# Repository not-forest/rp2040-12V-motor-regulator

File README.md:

# RP2040-Zero Powered 12V Motor Controller

RP2040 microcontroller handles status LEDs, an H-Bridge driver, and a rotary encoder input. RP2040's **PIO** is used to read encoder signals as a state machine, completely restraining bouncing errors from the input lines. This allows to use cheap encoders and have an amazing precision.

---

---

### PCB
- Designed in **KiCad**.
- Screw terminals 12V power input and motor output.
- Two versions include buck converter and linear regulator.

---

## Software
1. **Rotary Encoder**:
   - PIO reads encoder signals and adjusts speed.
2. **Rotary Encoder's Switch**:
   - Changes motor direction via the H-Bridge.
3. **PWM**:
   - Controls motor speed by adjusting duty cycles.
4. **Status LEDs**:
   - Show real-time speed and direction updates.

---

### Requirements
- **Rust Toolchain**: For building firmware.
- **elf2uf2-rs**: To flash the RP2040 (`cargo run` automatically searches for connected rp2040 and flashes thefirmware).
- **KiCad**: adjust PCB design.

---

Provides a reference for PIO-based rotary encoder handling in Rust.

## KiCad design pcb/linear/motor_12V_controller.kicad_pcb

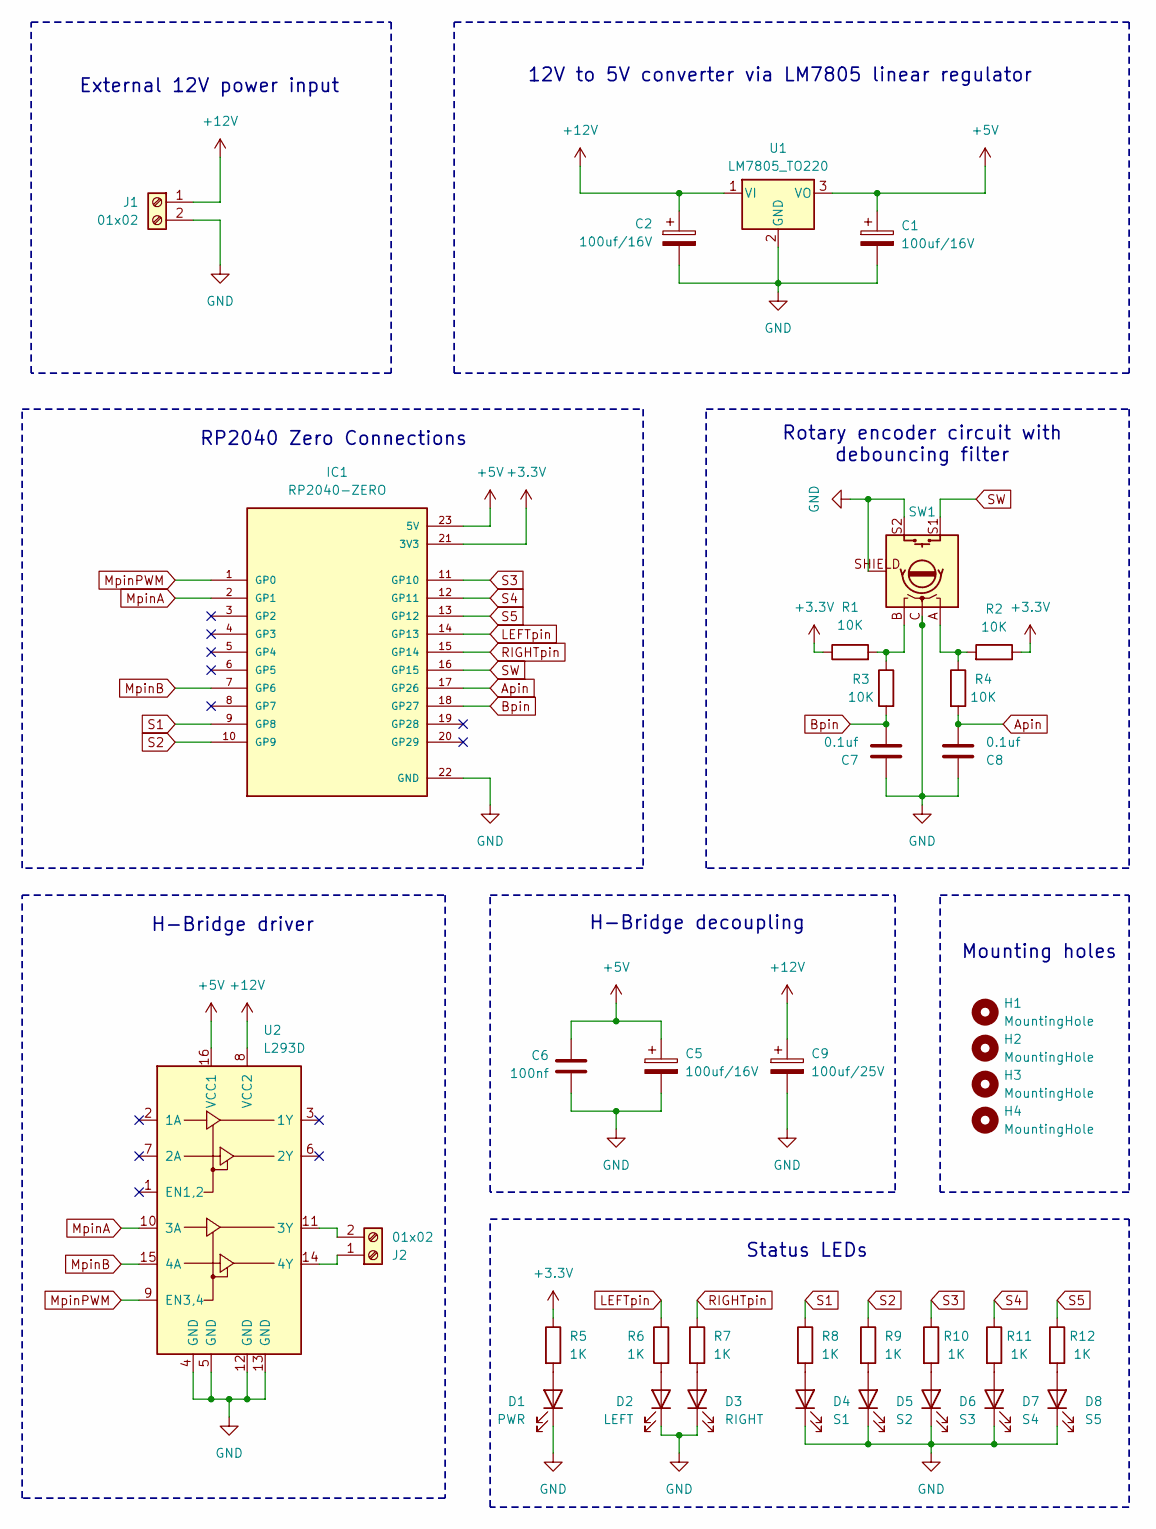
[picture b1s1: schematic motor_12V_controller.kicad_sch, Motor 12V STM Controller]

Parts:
C1, C2: 100uf/16V; C_Disc_D3.0mm_W1.6mm_P2.50mm
C5: 100uf/16V; C_Disc_D3.0mm_W2.0mm_P2.50mm
C6: 100nf; CP_Radial_D4.0mm_P1.50mm
C7, C8: 0.1uf; CP_Radial_D4.0mm_P1.50mm
C9: 100uf/25V; C_Disc_D3.0mm_W2.0mm_P2.50mm
D1: PWR; LED_Rectangular_W5.0mm_H2.0mm
D2: LEFT; LED_Rectangular_W5.0mm_H2.0mm
D3: RIGHT; LED_Rectangular_W5.0mm_H2.0mm
D4: S1; LED_Rectangular_W5.0mm_H2.0mm
D5: S2; LED_Rectangular_W5.0mm_H2.0mm
D6: S3; LED_Rectangular_W5.0mm_H2.0mm
D7: S4; LED_Rectangular_W5.0mm_H2.0mm
D8: S5; LED_Rectangular_W5.0mm_H2.0mm
H1, H2, H3, H4: MountingHole; MountingHole_2.2mm_M2
IC1: RP2040-ZERO; MODULE_RP2040-ZERO; PARTREV NA
J1, J2: 01x02; TerminalBlock_Xinya_XY308-2.54-2P_1x02_P2.54mm_Horizontal
R1, R2, R3, R4: 10K; R_Axial_DIN0204_L3.6mm_D1.6mm_P2.54mm_Vertical
R5, R6, R7, R8, R9, R10, R11, R12: 1K; R_Axial_DIN0204_L3.6mm_D1.6mm_P2.54mm_Vertical
SW1: XDCR_PEC11R-4215F-S0024
U1: LM7805_TO220; TO-220-3_Vertical
U2: L293D; DIP-16_W7.62mm_LongPads

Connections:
+3.3V: IC1.21 (3V3), R1.1, R2.1, R5.1
+5V: C1.1, C5.1, C6.1, IC1.23 (5V), U1.3 (VO), U2.16 (VCC1)
+12V: C2.1, C9.1, J1.1, U1.1 (VI), U2.8 (VCC2)
Apin: C8.2, IC1.17 (GP26), R4.2
Bpin: C7.2, IC1.18 (GP27), R3.2
GND: C1.2, C2.2, C5.2, C6.2, C7.1, C8.1, C9.2, D1.1 (K), D2.1 (K), D3.1 (K), D4.1 (K), D5.1 (K), D6.1 (K), D7.1 (K), D8.1 (K), IC1.22 (GND), J1.2, SW1.C, SW1.S2, SW1.SHIELD, U1.2 (GND), U2.4 (GND), U2.5 (GND), U2.12 (GND), U2.13 (GND)
LEFTpin: IC1.14 (GP13), R6.1
MpinA: IC1.2 (GP1), U2.10 (3A)
MpinB: IC1.7 (GP6), U2.15 (4A)
MpinPWM: IC1.1 (GP0), U2.9 (EN3,4)
unnamed: D1.2 (A), R5.2
unnamed: D2.2 (A), R6.2
unnamed: D3.2 (A), R7.2
unnamed: D4.2 (A), R8.2
unnamed: D5.2 (A), R9.2
unnamed: D6.2 (A), R10.2
unnamed: D7.2 (A), R11.2
unnamed: D8.2 (A), R12.2
unnamed: J2.1, U2.14 (4Y)
unnamed: J2.2, U2.11 (3Y)
unnamed: R1.2, R3.1, SW1.B
unnamed: R2.2, R4.1, SW1.A
RIGHTpin: IC1.15 (GP14), R7.1
S1: IC1.9 (GP8), R8.1
S2: IC1.10 (GP9), R9.1
S3: IC1.11 (GP10), R10.1
S4: IC1.12 (GP11), R11.1
S5: IC1.13 (GP12), R12.1
SW: IC1.16 (GP15), SW1.S1

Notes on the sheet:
Mounting holes
Rotary encoder circuit with debouncing filter
12V to 5V converter via LM7805 linear regulator
External 12V power input
RP2040 Zero Connections
H-Bridge decoupling
H-Bridge driver
Status LEDs

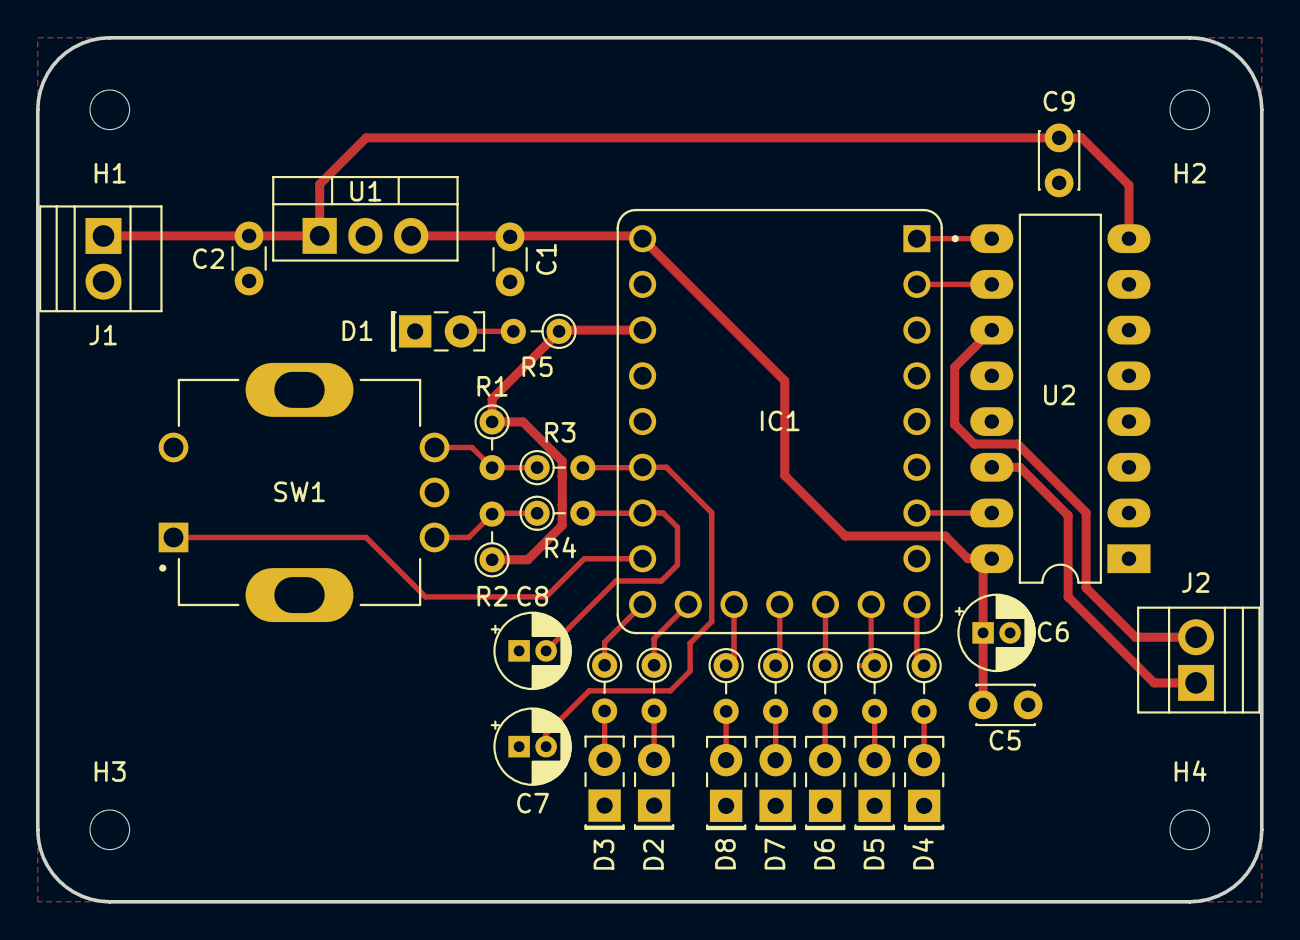
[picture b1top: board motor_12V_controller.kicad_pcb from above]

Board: 2 copper layers, 68.0 x 48.0 mm, 37 parts (0 on the bottom side), 29 nets.

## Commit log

2024-10-31 Added the first schematic layout and RP2040 Zero symbol file.
2024-10-31 Swapped the connections to to create more compact PCB design.
2024-10-31 Added more symbols and 3d models for PCB design.
2024-10-31 Added the first PCB design layout for a single layered, SMD, ground plane solution. Some changes might appear when implementing the source code or searching for components.
2024-10-31 Added the minimal rp2040 firmware code.
2024-10-31 Added the memory layout linker script stub for rp2040.
2024-10-31 Configuration for flashing hardware onto the ARM M0 core in RP2040.
2024-11-02 Got rid of printing libraries.
2024-11-02 Removed the probe flashing and defmt environment constant.
2024-11-02 Loading the setup and jumping to the main loop. Included new modules.
2024-11-02 Added module that describes the current motor driver's configuration and a set of functions to modify it.
2024-11-02 Defines all constant GPIO IDs with names for current circuit implementation.
2024-11-02 Written the GPIO setup part. Configured output and input pins with interrupts.
2024-11-03 Fixed the pullup bug on the switch pin, which was caused due to the default pulldown defined in the reference manual. Implemented a properly working direction switching mechanism via interrupts. Now 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
2024-11-03 Increased the speed step for each encoder's rotation. For leds using 6 possible states to include the state where no leds are used.
2024-11-03 Added a proper interrupt handling for encoder's A and B pins.
2024-11-03 Changed the rotary encoder's circuit part to use 3.3V voltage logic, since it is connected toRP2040 pins.
2024-11-03 Fixed the PCB according to new 3.3V connections.
2024-11-03 Changed the leds updating function to do it within the function itself, with provided SIO block.
2024-11-03 Moved the bootloader and panic handler to the main module.
2024-11-03 Added the PWM management based on the required implementation.
2024-11-04 Added one more interrupt mask for Bpin
2024-11-04 Causing two interrupts on both Apin and Bpin and progressing the state machine.
2024-11-04 The speed adjustment function implementation is now changed to a state machine of a rotary encoder. It is still not sufficient enough to prevent all bouncing problems a regular encoders have.
2024-11-04 Added clock switching setup routine to properly output 20kHz signal from the PWM pin for quiet motor.
2024-11-06 Updated the schematic for better match of footprints for tht elements.
2024-11-06 Swapped the SMD schematic to the THT one. Adjusted the AP632xx circuit according to the layout specified in the datasheet.
2024-11-06 Fixed the H-Bridge decoupling. Added additional capasitor for +12V power input.
2024-11-07 Stripped the pcb and schematics into linear and buck for different 12V to 5V converters.
2024-11-07 Removed items.
2024-11-07 Moved the PWM setup to the it's own module.
2024-11-07 Moved the external oscillator setup to the it's own module.
2024-11-07 Including new modules in the root module.
2024-11-07 Moved the gpio setup to the it's own module.
2024-11-07 Moved the setup functions to their own modules. Using motor structure as an interface to mutate the state of the system.
2024-11-07 Now motor structure owns the SIO and PWM interfaces allowing to hide the logic behind it.
2024-11-09 Changed the symbols for THT ceramic capacitors footprint. Swapped the footprints on the PCB design
2024-11-09 Added additional RC filtering for the encoder's switch.
2024-11-10 Added new pio-rs dependency for assembling .pio assembler programs.
2024-11-10 Removed interrupts from APIN and BPIN. Now encoder is managed fully by the PIO block.
2024-11-10 Added new modules. Removed the unecessary core variable.
2024-11-10 State machine logic is fully reimplemented and moved for PIO to handle separately from the main core. Major changes in update functions.
2024-11-10 State machine logic is fully reimplemented and moved for PIO to handle separately from the main core. IRQ0 and IRQ1 obtained from the PIO0 is now used to increment and decrement the PWM. Encoder is n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
2024-11-10 Added PIO setup module. It configures PIO block and one of it's state machines to run custom assembler code for managing the rotary encoder fully.
2024-11-10 Added the pio assembler code for handling the rotary encoder. Jump table is being used to handle every possible state of encoder. Counters are used for debouncing.
2024-11-12 Removed the unsafe blocks by rewriting with safer variant method.
2024-11-12 Removed the unecessary RC filter. Purely software debouncing will be used for the switch interface.
2024-11-25 Add docs
2024-12-14 Using edge interrupt on SW pin for debouncing.
2024-12-14 Additional debouncing delay for the switch button handling. Now using edge interrupt to prevent additional jumps between the latches.
